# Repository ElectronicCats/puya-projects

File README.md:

# PUYA Projects
PUYA projects is an experiment to use low-cost ARM PUYA microcontrollers.

## PY32F002A key features and specifications:

- MCU Core – 32-bit Arm Cortex-M0+ @ 24 MHz
- Memory – 3KB SRAM
- Storage – 20KB flash
- Peripherals:
  - 5 GPIOs (PF0, PA1, PA5, PA6, PA7)
  - 1x USART
  - 1x I2C, 1x SPI,  1x PWM (PA1 AF13 TIM1_CH4)
  - Up to 9-channel 12-bit ADC
- Timers
  - 1x general-purpose 16-bit timers
  - 1x 16-bit advanced control timer
  - 1x low-power timer (LPTIM) to support wake-up from stop mode
  - 1x SysTick timer
  - 1x watchdog timers (IWDT)
- Clocks
  - 4/24MHz RC (HSI)
  - 32.768KHz RC (LSI)
  - 4~24MHz HSE (External crystal oscillator)
  - Supply Voltage – 1.7V to 5.5V DC
  - Packages – SOP8 (4.9×3.7×1.75 mm), SOP16, ESSOP10, TSSOP20
  - Temperature Range – – 40°C to +85°C

## FOR WINDOWS
## Requirements
- PUYA microcontroller (We used a PUYA Dev Board with a PY32F002AA15M6TU microcontroller)
- J-Link Segger Debugger
- Visual Studio Code (mandatory)
- Git (Recommended)

## Tools Installation
1. **Install GNU Arm Embedded Toolchain:**
   - Download the appropriate version from [Arm GNU Toolchain Downloads](https://developer.arm.com/tools-and-software/open-source-software/developer-tools/gnu-toolchain/gnu-rm/downloads) (We use arm-none-eabi v12.3 rel1).
   - Add the tool's binary directory to the Windows PATH.

   To add the environment variable we look in the windows bar: "Edit environment variables for your account".

<p align="center">
   
   <div align="center">
      <sup><sub>Open "Edit environment variables for your account".</sub></sup>
   </div>
 </p>
    
 <p align="center">
    
    <div align="center">
      <sup><sub>Open "Environment Variables...".</sub></sup>
    </div>
 </p>

<p align="center">
    
   <div align="center">
      <sup><sub>Select "Path" and then "Edit...".</sub></sup>
    </div>
 </p>

 <p align="center">
    
   <div align="center">
      <sup><sub>Add "New" variable and add the path: "C:\Program Files (x86)\Arm GNU Toolchain arm-none-eabi\12.3 rel1\bin".</sub></sup>
    </div>
 </p>

2. **Open the Command Line:**
To open the "Command Line" search "cmd" or "PowerShell" in your windows bar. In this case "Windows PowerShell" was used, and a window like the following should open:

3. **Verify GNU Toolchain Installation:**
In your Command Line verify if GNU Toolchain Installation was correct.
   ```powershell
   &"C:\Program Files (x86)\Arm GNU Toolchain arm-none-eabi\12.3 rel1\bin\arm-none-eabi-gcc" -v 
   ```
   If it has been installed correctly you should obtain a result similar to the following:

4.  **Install Make:**
    -   Download Make from [GnuWin](http://gnuwin32.sourceforge.net/packages/make.htm).
    -   Add Make to the environment variables.

5.  **Check Make Installation:**
     ```powershell
     make -v
    
5.  **Install SEGGER J-Link:**
    -   Download from [J-Link / J-Trace Downloads](https://www.segger.com/downloads/jlink).
    -   Install J-Link tools.

## Project Configuration

1.  **Clone the PY32 Examples Repository:**
    Copy code
    
    `git clone https://github.com/TDLOGY/py32f0-template-project` 
    
2.  **Copy the JLinkDevices Directory:** Copy `[PY32 Directory]/Misc/Flash/JLinkDevices` to `C:\Users\[User]\AppData\Roaming\SEGGER\JLinkDevices\`.
    
3. **Find the JLink Path:** Locate the path where JLink is installed, typically something like: `"C:\Program Files\SEGGER\JLink\JLink"`. Save it for future configurations.

4.  **Connect J-Link and Verify:** In Windows PowerShell, use the following command to verify the J-Link connection:
    
    ```powershell
       &"C:\Program Files\SEGGER\JLink\JLink"
    ```

5.  **Open Visual Studio Code:**

    -   Open the `py32f0-template-project` folder.
    
6.  **Adjust Makefile for Your Chip** (The "Makerfile" is located in the project folder):

<p align="center">
   
   <div align="center">
      <sup><sub>Located in the project folder.</sub></sup>
   </div>
 </p>
   <ul>
      <ul>
         <li>Edit the Makefile to change the tools references, it uses the path references of the previously installed tools.</li>
      </ul>
   </ul> 

<p align="center">
   
   <div align="center">
      <sup><sub>Tools references.</sub></sup>
   </div>
 </p>

   <ul>
      <ul>
         <li>Edit the Makefile to change all the chip reference to `"PY32F002AX5"`.</li>
      </ul>
   </ul> 
    
7.  **Compile the Project:**
   
    -   In Visual Studio Code open a terminal.

<p align="center">
   
   <div align="center">
      <sup><sub>Opening a Terminal.</sub></sup>
   </div>
 </p>

  <ul>
      <ul>
         <li> Execute: <code> make -j4 </code> in the Visual Studio Code (VSC) terminal and verify that it compiles correctly, otherwise, it could be that the "Makefile" has not been configured correctly.</li>
      </ul>
   </ul>  

8.  **Modify the Code:**
    -   Open the `/User/main.c` file.
    -   Adjust pin references from ports B and F to A as needed.
  
9.  **Compile Again:** Execute `make clean` to clean the compilation and after `make -j4` to compile with the changes made.
    
10.  **Program the Board:** Use `make flash` to upload the code to your board using J-Link. (You must have your J-Link connected to your computer and with the corresponding connections to the development board)
    
11.  **Save Your Changes:** Remember to save the modified files before compiling.
    
12.  **Clean Previous Compilation:** If you make changes to the code, run `make clean` before compiling again.

PUYA Dev Board with the PY32F002AA15M6TU microcontroller should now be configured and ready to go!

**The development board can be programmed via SWD by a J-Link** (The J-link connections will depend on which J-Link and connector you are going to use).

### What is SWD?
SWD is a bidirectional communication protocol that allows for fast and efficient microcontroller debugging and programming.

SWD uses two signal lines, one for data (SWDIO) and one for clock (SWCLK), to communicate with the microcontroller. Through these lines, you can load programs into the microcontroller, stop code execution to inspect variables and debug errors, and perform other debugging operations. It is faster and more efficient than older debugging methods, such as JTAG.

## J-Link Connections to the Dev Board
As mentioned earlier, SWD communication involves two key lines: **SWDIO** for data and **SWCLK** for the clock signal. However, in addition to these two lines, we also require two more connections:

- **GND (Ground)**: This connection is essential to establish a common reference point for electrical potential and ensure proper communication.
- **VRef (Voltage Reference)**: In this case, our PUYA Dev board works with a logical voltage level of 3.3V so it is necessary to provide this voltage to the J-Link tool. This voltage, known as VRef, is necessary to support the communication between the J-Link and the target board.

**Note:** You need to power up the PUYA Dev board with an external 5V power supply.

### Instructions to use the J-Link PLUS Compact
To program the PUYA Dev Board with the J-Link PLUS Compact we will need the following components:
<div align="center">
   <table>
        <tr>
           <td>  
               <div align="center"><sup><sub>USB Cable.</sub></sup></div>
            </td>
            <td>
               <div align="center"><sup><sub>J-Link PLUS Compact.</sub></sup></div>
            </td>
           <td>
               <div align="center"><sup><sub>Dupont Wires.</sub></sup></div>
            </td>
        </tr>
   </table>
</div>

In addition to this, in order to make the connections we must know what the J-Link pinout is, take the image below as a reference and connect each wire from your PUYA Dev Board to the corresponding one on the J-Link:
<p align="center">
   
   <div align="center">
      <sup><sub>J-Link PLUS Compact connector.</sub></sup>
   </div>
 </p>

### Instructions to use the J-Link EDU Mini:
To program the PUYA Dev Board with the J-Link EDU Mini we will need the following components:
<div align="center">
   <table>
        <tr>
           <td>  
               <div align="center"><sup><sub>USB Cable.</sub></sup></div>
            </td>
            <td>  
               <div align="center"><sup><sub>J-Link EDU Mini.</sub></sup></div>
            </td>
           <td>
               <div align="center"><sup><sub>J-Link EDU Mini PCB Adapter.</sub></sup></div>
            </td>
            <td>
               <div align="center"><sup><sub>J-Link EDU Mini Cable.</sub></sup></div>
            </td>
           <td>
               <div align="center"><sup><sub>Dupont Wires.</sub></sup></div>
            </td>
        </tr>
   </table>
</div>

As shown in the required material, the J-Link EDU Mini PCB Adapter helps us a lot in identifying where we need to connect each wire from our PUYA development board to the PCB adapter. After connecting the corresponding wires you can program your board.

### Connection example:
<p align="center">
   
   <div align="center">
      <sup><sub>Illustrative image of connections.</sub></sup>
   </div>
 </p>

The image above is just a reference image of the connections.
The board is being powered directly with 5V and there are the following connections:
<div align="center">
   <table>
      <tr>
       <th>PUYA Dev Board</th>
       <th>J-Link Compact</th>
       <th>J-Link EDU</th>
       <th>Power Supply</th>
     </tr>
     <tr>
       <td>3.3V</td>
       <td>VTref</td>
       <td>Vref</td>
       <td>X</td>
     </tr>
     <tr>
       <td>GND</td>
       <td>GND</td>
       <td>GND</td>
       <td>GND</td>
     </tr>
     <tr>
       <td>DIO</td>
       <td>SWDIO</td>
       <td>SWIO</td>
       <td>X</td>
     </tr>
     <tr>
       <td>CLK</td>
       <td>SWCLK</td>
       <td>CLK</td>
       <td>X</td>
     </tr>
     <tr>
       <td>5V</td>
       <td>X</td>
       <td>X</td>
       <td>5V</td>
     </tr>
   </table>
</div>

## Thanks / Contributors
This example is based on the [Example Code PY32F0](https://github.com/TDLOGY/py32f0-template-project/tree/618b7ab8a95be73d5871b39afd02e14fb6a823dd)

## Maintainer

<div align="center">
   
</div>
Electronic Cats invests time and resources providing this open source design, please support Electronic Cats and open-source hardware by purchasing products from Electronic Cats!

[Agregando el link como referencia]: <https://github.com/ElectronicCats/Template-Project-KiCAD-CI>

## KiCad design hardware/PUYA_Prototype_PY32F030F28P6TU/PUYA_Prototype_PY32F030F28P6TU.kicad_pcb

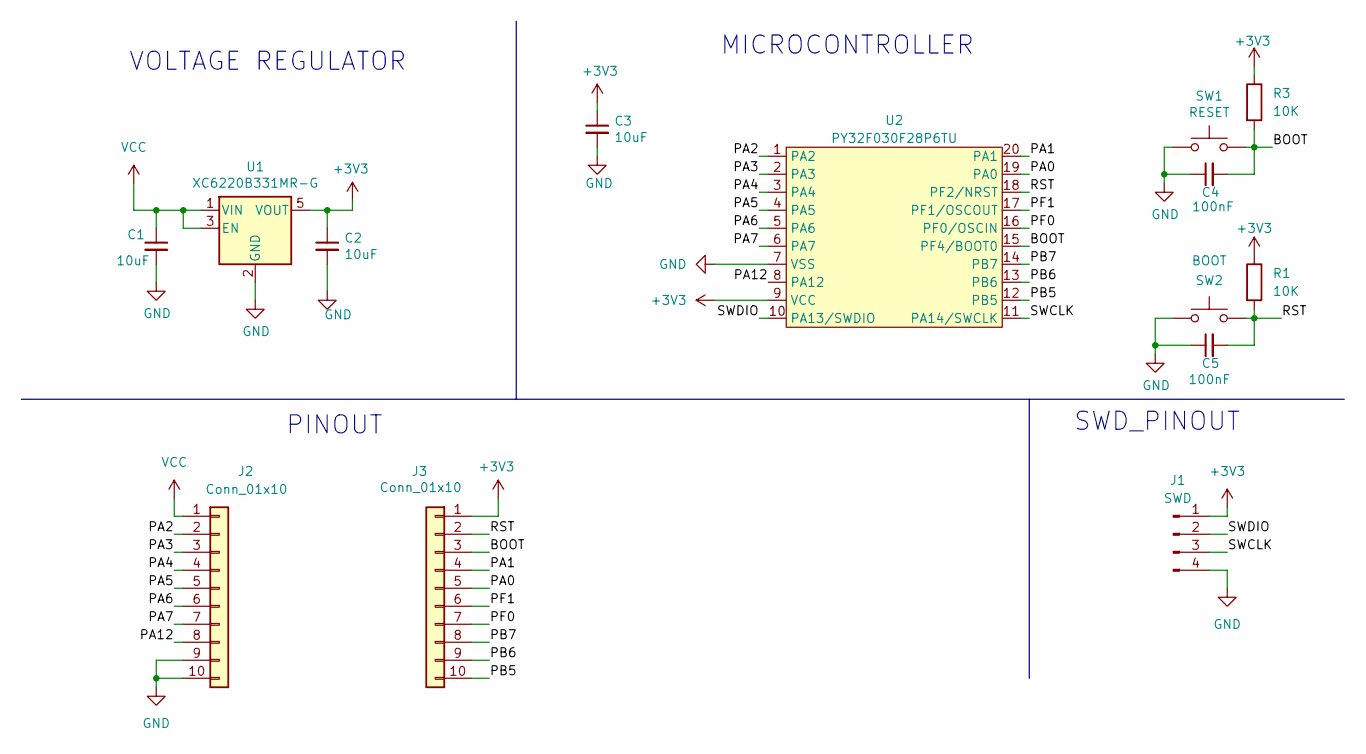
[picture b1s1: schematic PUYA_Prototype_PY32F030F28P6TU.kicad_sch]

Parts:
C1, C2, C3: 10uF; C_0603_1608Metric; LCSC# C85713
C4, C5: 100nF; C_0603_1608Metric; LCSC# C478888
J1: SWD; PinHeader_1x04_P2.54mm_Vertical
J2, J3: Conn_01x10; PinHeader_1x10_P2.54mm_Vertical
R1, R3: 10K; R_0603_1608Metric; LCSC# C217281
SW1: RESET; TS1088R02026; LCSC# C318889
SW2: BOOT; TS1088R02026; LCSC# C318889
U1: XC6220B331MR-G; SOT-23-5; LCSC# C86534
U2: PY32F030F28P6TU; TSSOP-20_4.4x6.5mm_P0.65mm; LCSC# C3018716

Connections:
+3V3: C2.1, C3.1, J1.1, J3.1, R1.1, R3.1, U1.5 (VOUT), U2.9 (VCC)
/BOOT: C4.2, J3.3, R3.2, SW1.2, U2.15 (PF4/BOOT0)
/PA0: J3.5, U2.19 (PA0)
/PA1: J3.4, U2.20 (PA1)
/PA2: J2.2, U2.1 (PA2)
/PA3: J2.3, U2.2 (PA3)
/PA4: J2.4, U2.3 (PA4)
/PA5: J2.5, U2.4 (PA5)
/PA6: J2.6, U2.5 (PA6)
/PA7: J2.7, U2.6 (PA7)
/PA12: J2.8, U2.8 (PA12)
/PB5: J3.10, U2.12 (PB5)
/PB6: J3.9, U2.13 (PB6)
/PB7: J3.8, U2.14 (PB7)
/PF0: J3.7, U2.16 (PF0/OSCIN)
/PF1: J3.6, U2.17 (PF1/OSCOUT)
/RST: C5.2, J3.2, R1.2, SW2.2, U2.18 (PF2/NRST)
/SWCLK: J1.3, U2.11 (PA14/SWCLK)
/SWDIO: J1.2, U2.10 (PA13/SWDIO)
GND: C1.2, C2.2, C3.2, C4.1, C5.1, J1.4, J2.9, J2.10, SW1.1, SW2.1, U1.2 (GND), U2.7 (VSS)
VCC: C1.1, J2.1, U1.1 (VIN), U1.3 (EN)

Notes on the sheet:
PINOUT
SWD_PINOUT
MICROCONTROLLER
VOLTAGE REGULATOR

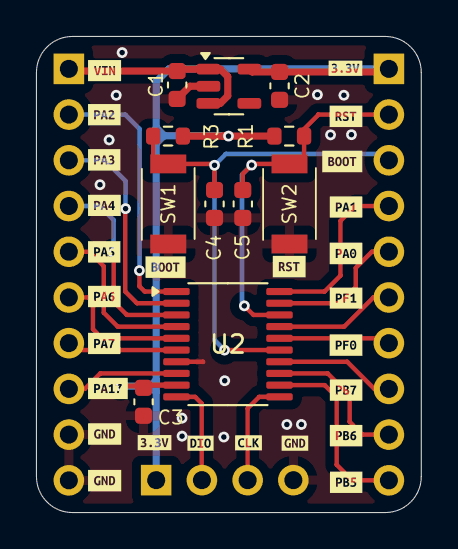
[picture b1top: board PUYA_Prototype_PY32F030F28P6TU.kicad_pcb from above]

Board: 2 copper layers, 21.4 x 26.4 mm, 40 parts (0 on the bottom side), 21 nets.

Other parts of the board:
kibuzzard-67B50BE4: G***; kibuzzard-67B50BE4
kibuzzard-67B50BE9: G***; kibuzzard-67B50BE9
kibuzzard-67B50BF3: G***; kibuzzard-67B50BF3
kibuzzard-67B50C0B: G***; kibuzzard-67B50C0B
kibuzzard-67B50C01: G***; kibuzzard-67B50C01
kibuzzard-67B50C2D: G***; kibuzzard-67B50C2D
kibuzzard-67B50C05: G***; kibuzzard-67B50C05
kibuzzard-67B50C7B: G***; kibuzzard-67B50C7B
kibuzzard-67B50C8C: G***; kibuzzard-67B50C8C
kibuzzard-67B50C9F: G***; kibuzzard-67B50C9F
kibuzzard-67B50C10: G***; kibuzzard-67B50C10
kibuzzard-67B50C14: G***; kibuzzard-67B50C14
kibuzzard-67B50C29: G***; kibuzzard-67B50C29
kibuzzard-67B50C61: G***; kibuzzard-67B50C61
kibuzzard-67B50C66: G***; kibuzzard-67B50C66
kibuzzard-67B50C75: G***; kibuzzard-67B50C75
kibuzzard-67B50C80: G***; kibuzzard-67B50C80
kibuzzard-67B50C92: G***; kibuzzard-67B50C92
kibuzzard-67B50C98: G***; kibuzzard-67B50C98
kibuzzard-67B50CD8: G***; kibuzzard-67B50CD8
kibuzzard-67B50CE1: G***; kibuzzard-67B50CE1
kibuzzard-646D3CA0: G***; kibuzzard-646D3CA0
kibuzzard-646D3CAB: G***; kibuzzard-646D3CAB
kibuzzard-646D3CBC: G***; kibuzzard-646D3CBC
kibuzzard-646D3CFD, kibuzzard-646D3CFD#2: G***; kibuzzard-646D3CFD

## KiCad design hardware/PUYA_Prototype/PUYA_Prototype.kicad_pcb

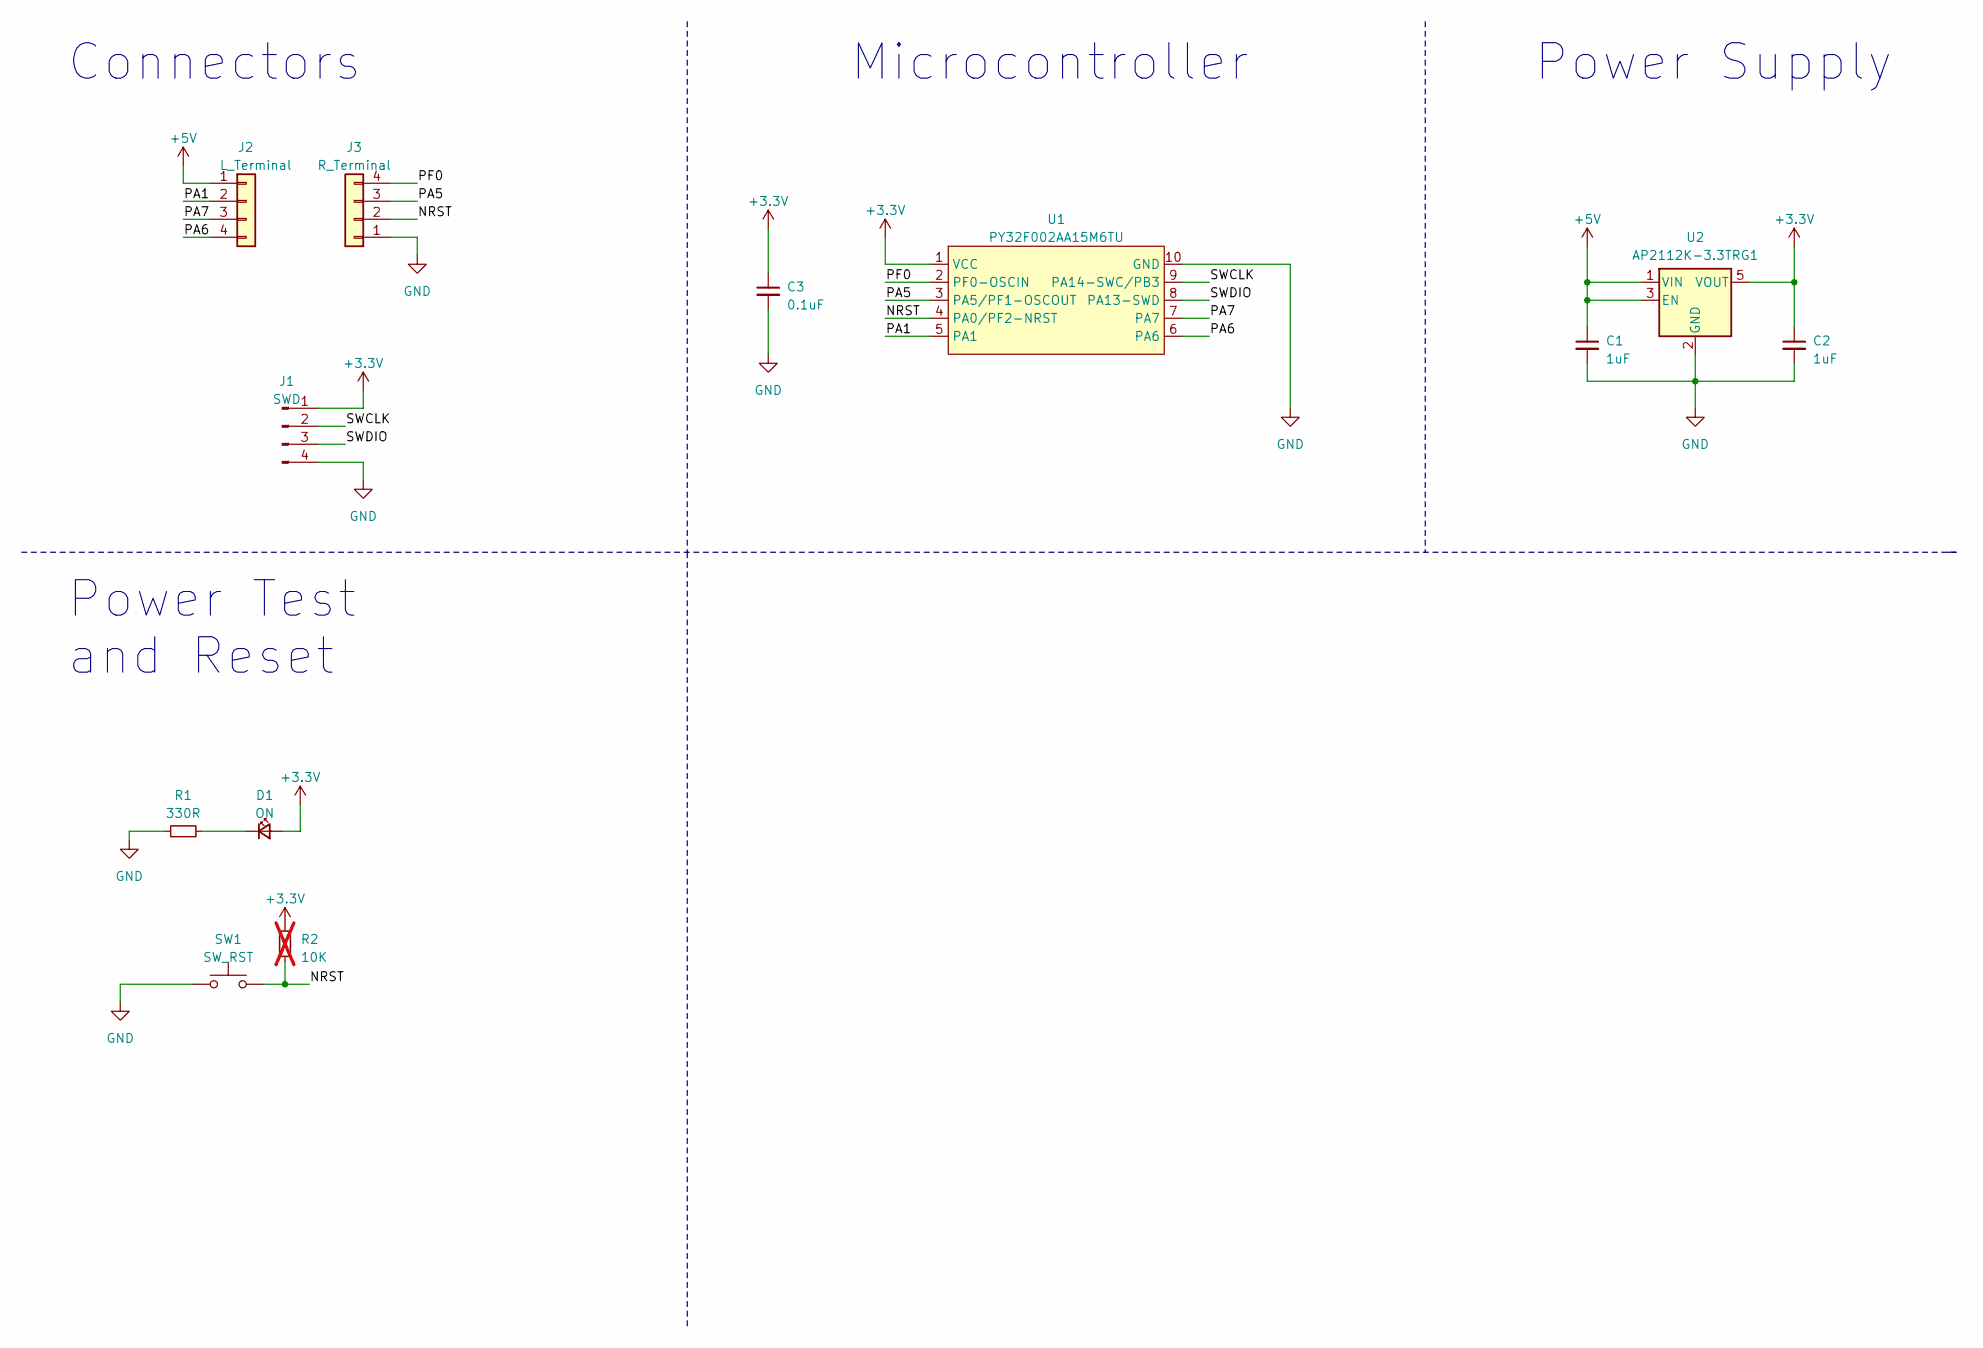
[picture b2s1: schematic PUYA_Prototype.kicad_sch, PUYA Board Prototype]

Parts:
C1, C2: 1uF; C_0805_2012Metric; LCSC# C24123
C3: 0.1uF; C_0805_2012Metric; LCSC# C360619
D1: ON; LED_0805_2012Metric; LCSC# C130114
J1: SWD; PinHeader_1x04_P2.54mm_Vertical
J2: L_Terminal; PinHeader_1x04_P2.54mm_Vertical
J3: R_Terminal; PinHeader_1x04_P2.54mm_Vertical
R1: 330R; R_0805_2012Metric; LCSC# C119075
R2: 10K; R_0805_2012Metric; LCSC# C99198; not fitted
SW1: SW_RST; SW_SPST_TL3342; LCSC# C318889
U1: PY32F002AA15M6TU; PY32F002AA15M; LCSC# C5292058
U2: AP2112K-3.3TRG1; TSOT-23-5

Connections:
+3.3V: C2.1, C3.1, D1.2 (A), J1.1, R2.2, U1.1 (VCC), U2.5 (VOUT)
+5V: C1.1, J2.1, U2.1 (VIN), U2.3 (EN)
/NRST: J3.2, R2.1, SW1.2, U1.4 (PA0/PF2-NRST)
/PA1: J2.2, U1.5 (PA1)
/PA5: J3.3, U1.3 (PA5/PF1-OSCOUT)
/PA6: J2.4, U1.6 (PA6)
/PA7: J2.3, U1.7 (PA7)
/PF0: J3.4, U1.2 (PF0-OSCIN)
/SWCLK: J1.2, U1.9 (PA14-SWC/PB3)
/SWDIO: J1.3, U1.8 (PA13-SWD)
GND: C1.2, C2.2, C3.2, J1.4, J3.1, R1.1, SW1.1, U1.10 (GND), U2.2 (GND)
unnamed: D1.1 (K), R1.2

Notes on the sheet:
Power Supply
Microcontroller
Power Test and Reset
Connectors

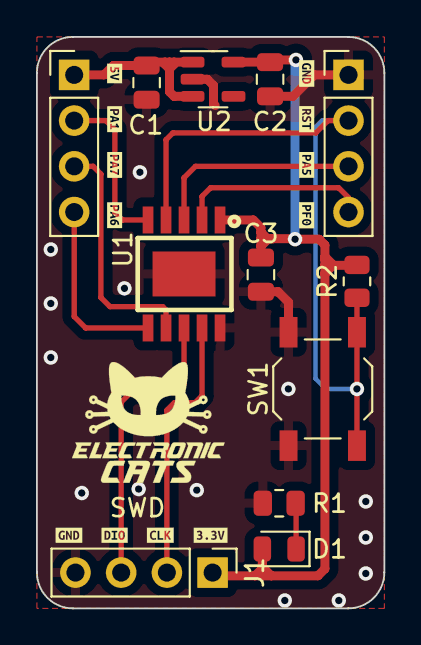
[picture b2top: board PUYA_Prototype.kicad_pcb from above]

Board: 2 copper layers, 19.3 x 31.8 mm, 24 parts (0 on the bottom side), 12 nets.

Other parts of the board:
kibuzzard-646D3A66: G***; kibuzzard-646D3A66
kibuzzard-646D3B4A: G***; kibuzzard-646D3B4A
kibuzzard-646D3B19: G***; kibuzzard-646D3B19
kibuzzard-646D3BD4: G***; kibuzzard-646D3BD4
kibuzzard-646D3C07: G***; kibuzzard-646D3C07
kibuzzard-646D3C24: G***; kibuzzard-646D3C24
kibuzzard-646D3C34: G***; kibuzzard-646D3C34
kibuzzard-646D3C54: G***; kibuzzard-646D3C54
kibuzzard-646D3CA0: G***; kibuzzard-646D3CA0
kibuzzard-646D3CAB: G***; kibuzzard-646D3CAB
kibuzzard-646D3CBC: G***; kibuzzard-646D3CBC
kibuzzard-646D3CFD: G***; kibuzzard-646D3CFD

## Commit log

2023-05-23 Boards first revision
2023-05-23 Board finished plus gerbers plus BOM
2023-06-02 Board tracks corrected
2023-06-05 fix traces and add EC symbols
2023-06-05 add pull-up resistor to NRST "DNP"
2023-06-05 add library.pretty
2023-06-05 fix library
2023-06-07 change edge cuts
2023-06-07 add "on" serigraphy to D1
2023-09-15 Update Configuration Steps
2023-09-27 Update README.md
    Added how to add environment variables and where the Makerfile is located
2023-10-05 Update README.md
    Additional information
2023-10-06 Update README.md
    Visual adjustments
2023-10-11 Connections Section created and developing
2023-10-19 What is SWD and how does it work?
2023-10-19 Updated connection instructions
2023-10-19 Added Illustrative image
2023-10-20 Updating necessary connections
2023-10-20 Added a connection table
2023-10-20 Alignment corrections
2024-02-20 Updating the information on the versions used
2024-03-27 chore: Update README.md
    Add PY32F002A characteristics
2024-04-02 chore: Update PUYA specification
2025-02-18 refactor: rename folder
2025-02-18 feat(hw): add schematic for prototype
2025-02-18 feat(hw): add pcb design
